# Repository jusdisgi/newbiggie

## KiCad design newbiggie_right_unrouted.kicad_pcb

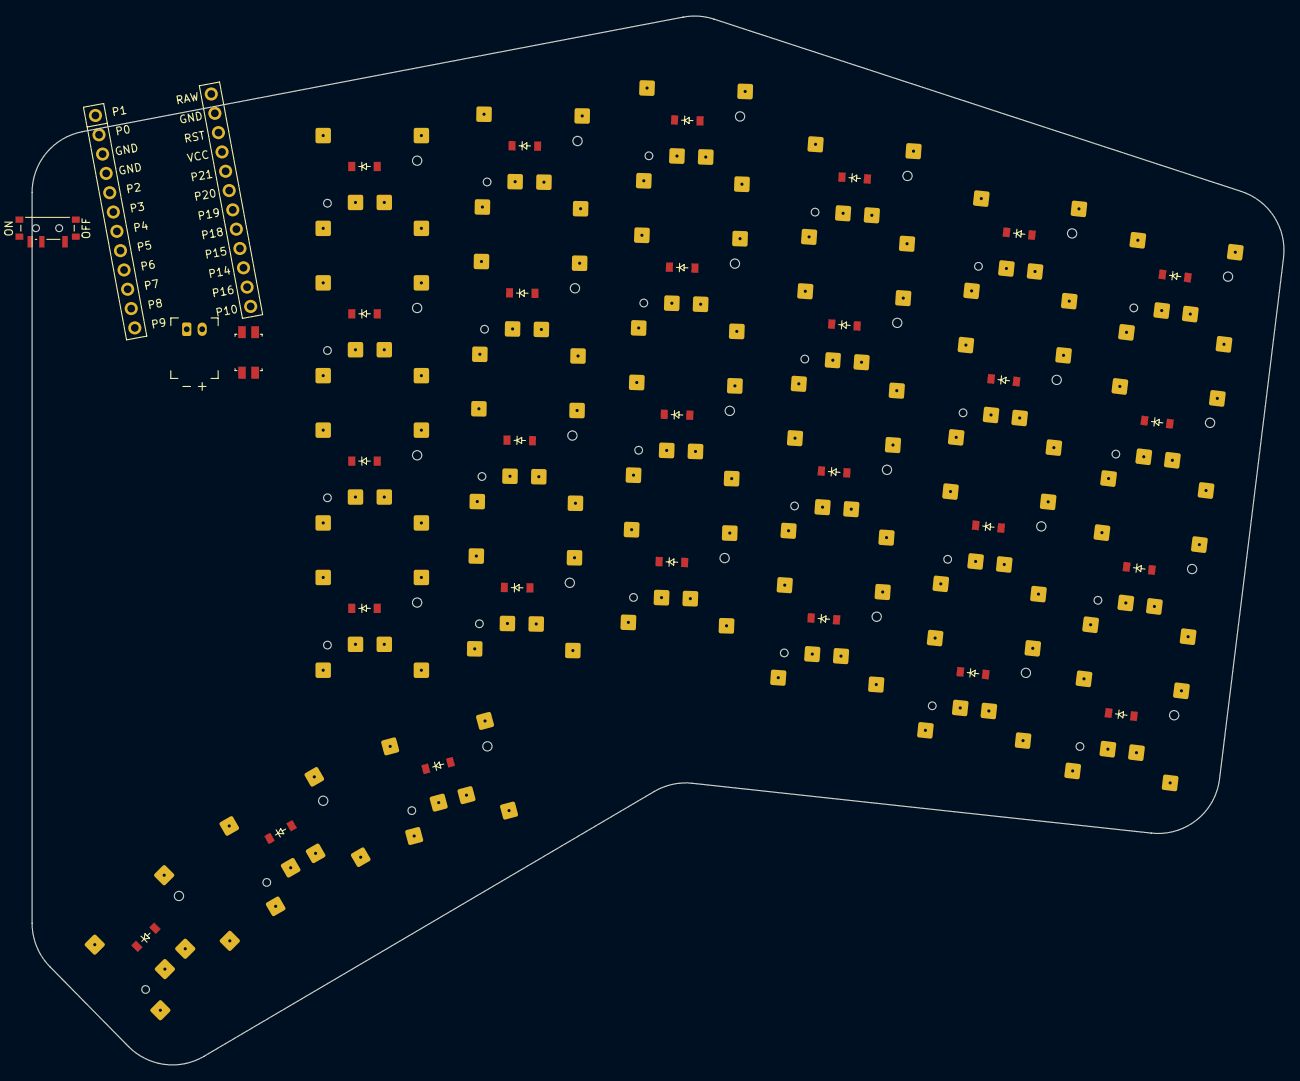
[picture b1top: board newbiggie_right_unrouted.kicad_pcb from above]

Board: 2 copper layers, 161.9 x 135.6 mm, 58 parts (0 on the bottom side), 43 nets, no tracks yet.

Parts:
D1, D2, D3, D4, D5, D6, D7, D8, D9, D10, D11, D12, D13, D14, D15, D16, D17, D18, D19, D20, D21, D22, D23, D24, D25, D26, D27: diode_tht_sod123
JST1: battery_connector_jst_ph_2
MCU1: mcu_nice_nano
PWR1: power_switch_smd_side
RST1: reset_switch_smd_side
S1, S2, S3, S4, S5, S6, S7, S8, S9, S10, S11, S12, S13, S14, S15, S16, S17, S18, S19, S20, S21, S22, S23, S24, S25, S26, S27: PG1316S

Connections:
BAT_P: JST1.2, PWR1.3
GND: JST1.1, MCU1.2, MCU1.21, MCU1.22, RST1.2, RST1.4
P2: MCU1.20, S1.1, S2.1, S3.1, S4.1
P3: MCU1.19, S5.1, S6.1, S7.1, S8.1
P4: MCU1.18, S9.1, S10.1, S11.1, S12.1, S25.1
P5: MCU1.17, S26.1
P6: MCU1.16, S13.1, S14.1, S15.1, S16.1, S27.1
P8: MCU1.14, S17.1, S18.1, S19.1, S20.1
P9: MCU1.13, S21.1, S22.1, S23.1, S24.1
P10: D1.1, D5.1, D9.1, D13.1, D17.1, D21.1, MCU1.12
P14: D3.1, D7.1, D11.1, D15.1, D19.1, D23.1, MCU1.10
P15: D4.1, D8.1, D12.1, D16.1, D20.1, D24.1, MCU1.9
P16: D2.1, D6.1, D10.1, D14.1, D18.1, D22.1, MCU1.11
P18: D25.1, D26.1, D27.1, MCU1.8
RAW: MCU1.1, PWR1.2
RST: MCU1.3, RST1.1, RST1.3
mirror_far_fan: D27.2, S27.2
mirror_index_bottom: D17.2, S17.2
mirror_index_high: D19.2, S19.2
mirror_index_home: D18.2, S18.2
mirror_index_num: D20.2, S20.2
mirror_inner_bottom: D21.2, S21.2
mirror_inner_high: D23.2, S23.2
mirror_inner_home: D22.2, S22.2
mirror_inner_num: D24.2, S24.2
mirror_mid_fan: D26.2, S26.2
mirror_middle_bottom: D13.2, S13.2
mirror_middle_high: D15.2, S15.2
mirror_middle_home: D14.2, S14.2
mirror_middle_num: D16.2, S16.2
mirror_near_fan: D25.2, S25.2
mirror_pinky_bottom: D5.2, S5.2
mirror_pinky_high: D7.2, S7.2
mirror_pinky_home: D6.2, S6.2
mirror_pinky_num: D8.2, S8.2
mirror_ring_bottom: D9.2, S9.2
mirror_ring_high: D11.2, S11.2
mirror_ring_home: D10.2, S10.2
mirror_ring_num: D12.2, S12.2
mirror_stretch_bottom: D1.2, S1.2
mirror_stretch_high: D3.2, S3.2
mirror_stretch_home: D2.2, S2.2
mirror_stretch_num: D4.2, S4.2

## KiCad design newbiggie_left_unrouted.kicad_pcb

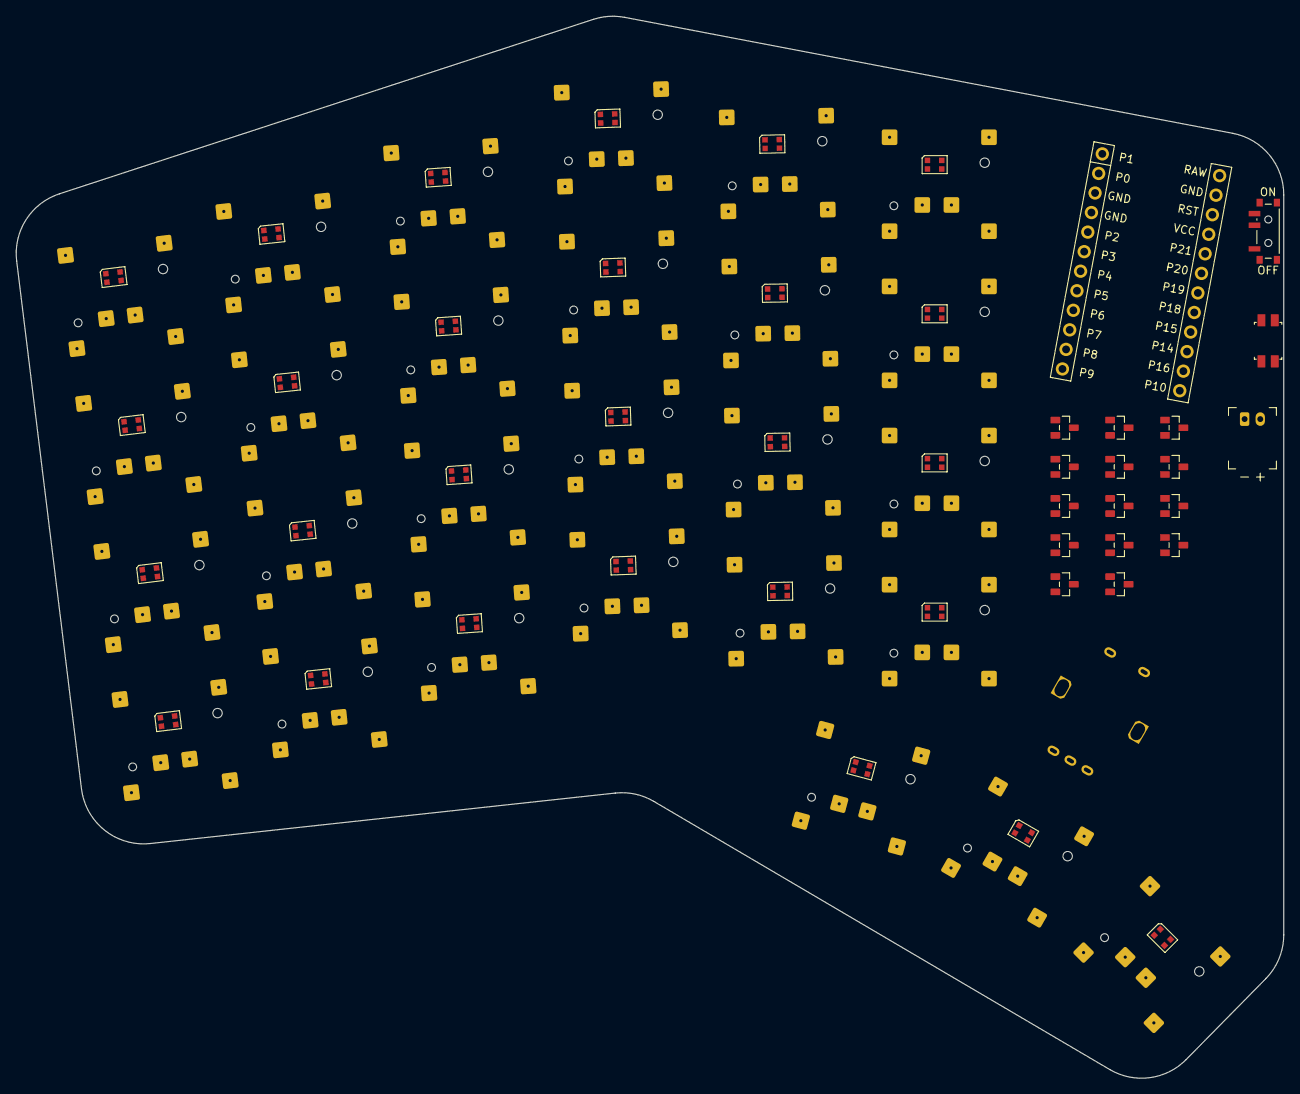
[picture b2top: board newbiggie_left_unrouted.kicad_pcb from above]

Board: 2 copper layers, 161.9 x 135.6 mm, 73 parts (0 on the bottom side), 44 nets, no tracks yet.

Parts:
D1, D2, D3, D4, D5, D6, D7, D8, D9, D10, D11, D12, D13, D14: BAV70; BAV70 SOT23
JST1: battery_connector_jst_ph_2
LED1, LED2, LED3, LED4, LED5, LED6, LED7, LED8, LED9, LED10, LED11, LED12, LED13, LED14, LED15, LED16, LED17, LED18, LED19, LED20, LED21, LED22, LED23, LED24, LED25, LED26, LED27: LED_WS2812B-2020_PLCC4_2.0x2.0mm
MCU1: mcu_nice_nano
PWR1: power_switch_smd_side
RE1: rotary_encoder_ec11_ec12
RST1: reset_switch_smd_side
S1, S2, S3, S4, S5, S6, S7, S8, S9, S10, S11, S12, S13, S14, S15, S16, S17, S18, S19, S20, S21, S22, S23, S24, S25, S26, S27: PG1316S

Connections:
BAT_P: JST1.2, PWR1.2
GND: JST1.1, LED1.3, LED2.3, LED3.3, LED4.3, LED5.3, LED6.3, LED7.3, LED8.3, LED9.3, LED10.3, LED11.3, LED12.3, LED13.3, LED14.3, LED15.3, LED16.3, LED17.3, LED18.3, LED19.3, LED20.3, LED21.3, LED22.3, LED23.3, LED24.3, LED25.3, LED26.3, LED27.3, MCU1.2, MCU1.21, MCU1.22, RE1.B, RST1.1, RST1.3
P2: LED1.2, LED2.2, LED3.2, LED4.2, LED5.2, LED6.2, LED7.2, LED8.2, LED9.2, LED10.2, LED11.2, LED12.2, LED13.2, LED14.2, LED15.2, LED16.2, LED17.2, LED18.2, LED19.2, LED20.2, LED21.2, LED22.2, LED23.2, LED24.2, LED25.2, LED26.2, LED27.2, MCU1.20, S1.1, S2.1, S3.1, S4.1
P3: MCU1.19, S5.1, S6.1, S7.1, S8.1
P4: LED1.4, LED2.4, LED3.4, LED4.4, LED5.4, LED6.4, LED7.4, LED8.4, LED9.4, LED10.4, LED11.4, LED12.4, LED13.4, LED14.4, LED15.4, LED16.4, LED17.4, LED18.4, LED19.4, LED20.4, LED21.4, LED22.4, LED23.4, LED24.4, LED25.4, LED26.4, LED27.4, MCU1.18, S9.1, S10.1, S11.1, S12.1, S25.1
P5: MCU1.17, S13.1, S14.1, S15.1, S16.1, S26.1
P6: MCU1.16, S27.1
P7: MCU1.15, S17.1, S18.1, S19.1, S20.1
P9: MCU1.13, RE1.S1, S21.1, S22.1, S23.1, S24.1
P10: D10.3, D11.3, D12.3, MCU1.12
P14: D4.3, D5.3, D6.3, MCU1.10
P15: D1.3, D2.3, D3.3, MCU1.9
P16: D7.3, D8.3, D9.3, MCU1.11
P18: D13.3, D14.3, MCU1.8
RAW: MCU1.1, PWR1.3
RST: MCU1.3, RST1.2, RST1.4
VCC: LED1.1, LED2.1, LED3.1, LED4.1, LED5.1, LED6.1, LED7.1, LED8.1, LED9.1, LED10.1, LED11.1, LED12.1, LED13.1, LED14.1, LED15.1, LED16.1, LED17.1, LED18.1, LED19.1, LED20.1, LED21.1, LED22.1, LED23.1, LED24.1, LED25.1, LED26.1, LED27.1, MCU1.4
far_fan: D14.1, S27.2
index_bottom: D12.1, S17.2
index_high: D6.1, S19.2
index_home: D9.1, S18.2
index_num: D3.1, S20.2
inner_bottom: D12.2, S21.2
inner_high: D6.2, S23.2
inner_home: D9.2, S22.2
inner_num: D3.2, S24.2
mid_fan: D13.2, S26.2
middle_bottom: D11.2, S13.2
middle_high: D5.2, S15.2
middle_home: D8.2, S14.2
middle_num: D2.2, S16.2
near_fan: D13.1, S25.2
pinky_bottom: D10.2, S5.2
pinky_high: D4.2, S7.2
pinky_home: D7.2, S6.2
pinky_num: D1.2, S8.2
ring_bottom: D11.1, S9.2
ring_high: D5.1, S11.2
ring_home: D8.1, S10.2
ring_num: D2.1, S12.2
stretch_bottom: D10.1, S1.2
stretch_high: D4.1, S3.2
stretch_home: D7.1, S2.2
stretch_num: D1.1, S4.2

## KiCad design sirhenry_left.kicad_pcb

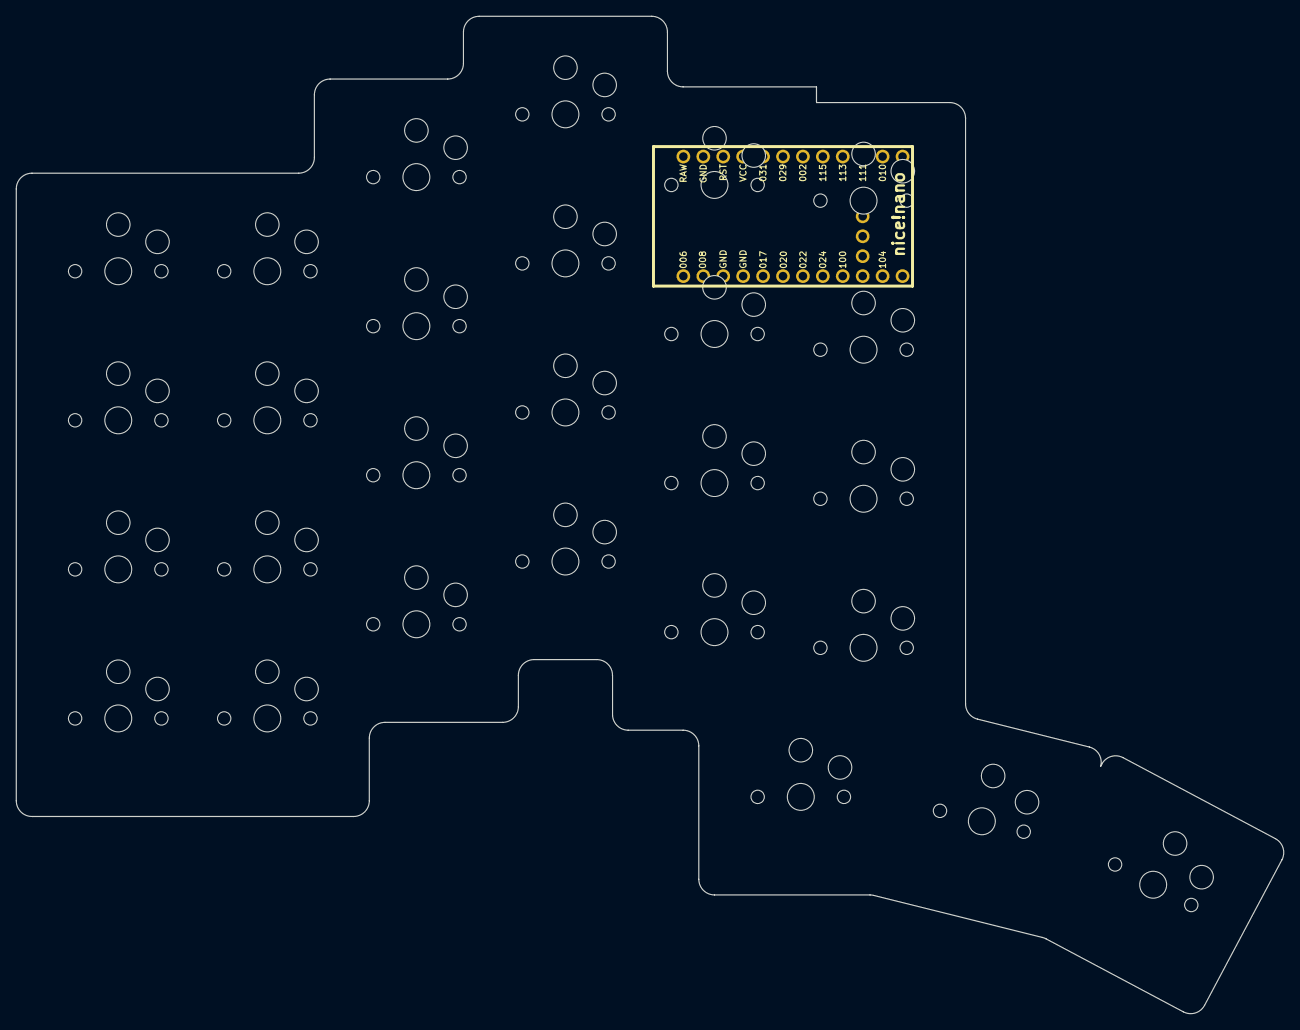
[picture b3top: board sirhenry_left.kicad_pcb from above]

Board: 2 copper layers, 161.6 x 127.1 mm, 28 parts (0 on the bottom side), 7 nets, no tracks yet.

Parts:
MCU1: nice_nano
S1, S2, S3, S4, S5, S6, S7, S8, S9, S10, S11, S12, S13, S14, S15, S16, S17, S18, S19, S20, S21, S22, S23, S24, S25, S26, S27: PG1350

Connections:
GND: MCU1.3, MCU1.4, MCU1.23
P011: MCU1.10, S17.1, S18.1, S19.1, S20.1, S26.1
P017: MCU1.5, S21.1, S22.1, S23.1, S24.1, S27.1
P020: MCU1.6, S1.1, S2.1, S3.1, S4.1
P022: MCU1.7, S5.1, S6.1, S7.1, S8.1
P024: MCU1.8, S9.1, S10.1, S11.1, S12.1
P100: MCU1.9, S13.1, S14.1, S15.1, S16.1, S25.1

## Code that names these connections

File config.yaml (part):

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        where: hand_inner_home
        params:
          A1: "stretch_num"
          A2: "pinky_num"
          C: "P15"
          side: F
        adjust:
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        where: hand_inner_home
        params:
          A1: "stretch_high"
          A2: "pinky_high"
          C: "P14"
          side: F
        adjust:
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        where: hand_inner_home
        params:
          A1: "stretch_home"
          A2: "pinky_home"
          C: "P16"
          side: F
        adjust:
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        where: hand_inner_home
        params:
          A1: "stretch_bottom"
          A2: "pinky_bottom"
          C: "P10"
          side: F
        adjust:
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
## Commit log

2025-05-24 Initial commit.
2025-05-30 I should do this more often.
